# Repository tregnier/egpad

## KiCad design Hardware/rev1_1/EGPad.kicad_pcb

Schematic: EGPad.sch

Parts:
C1, C2, C3, C4, C5, C6: 10nF; C_0603
D1, D2, D3, D4, D5, D6, D7, D8, D9, D10, D11, D12, D13, D14, D15, D16, D17, D18, D19, D20: D_Small; MD_Diode
J1: OLED
JP1, JP2, JP3, JP4, JP5, JP6, JP7, JP8: Jmp; Jumper
MX1, MX2, MX3, MX4, MX6, MX7, MX8, MX9, MX10, MX11, MX12, MX13, MX14, MX15: MX-NoLED; MX_ALPS_PG1350_noLed
MX5: MX-NoLED; MX-2U-NoLED
MX16, MX17: MX-NoLED; Hybrid_PCB_200V
R1, R2, R3, R4, R5, R6, R7, R8, R9, R10, R11, R12: 10k; Resistor
R13, R14: R
RSW1: SW_Push; ResetSW
SW1, SW2, SW3: Rotary_Encoder_Switch; RotaryEncoder_EC11
U1: ProMicro; ProMicro_v2

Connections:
A1: C1.1, R1.1, U1.1
A2: C3.1, R3.1, U1.2
A3: C5.1, R5.1, U1.7
B1: C2.1, R2.1, U1.20
B2: C4.1, R4.1, U1.19
B3: C6.1, R6.1, U1.18
COL1: MX1.1 (COL), MX2.1 (COL), MX3.1 (COL), MX4.1 (COL), MX5.1 (COL), U1.8
COL2: MX6.1 (COL), MX7.1 (COL), MX8.1 (COL), MX9.1 (COL), MX10.1 (COL), U1.9
COL3: MX11.1 (COL), MX12.1 (COL), MX13.1 (COL), MX14.1 (COL), U1.10
COL4: MX15.1 (COL), MX16.1 (COL), MX17.1 (COL), U1.11
COL5: SW1.S1, SW2.S1, SW3.S1, U1.12
GND: C1.2, C2.2, C3.2, C4.2, C5.2, C6.2, JP1.2, JP8.2, RSW1.2, SW1.C, SW2.C, SW3.C, U1.3, U1.4, U1.23
unnamed: D1.2, MX1.2 (ROW)
unnamed: D2.2, MX2.2 (ROW)
unnamed: D3.2, MX3.2 (ROW)
unnamed: D4.2, MX4.2 (ROW)
unnamed: D5.2, MX5.2 (ROW)
unnamed: D6.2, MX6.2 (ROW)
unnamed: D7.2, MX7.2 (ROW)
unnamed: D8.2, MX8.2 (ROW)
unnamed: D9.2, MX9.2 (ROW)
unnamed: D10.2, MX10.2 (ROW)
unnamed: D11.2, MX11.2 (ROW)
unnamed: D12.2, MX12.2 (ROW)
unnamed: D13.2, MX13.2 (ROW)
unnamed: D14.2, MX14.2 (ROW)
unnamed: D15.2, MX15.2 (ROW)
unnamed: D16.2, MX16.2 (ROW)
unnamed: D17.2, MX17.2 (ROW)
unnamed: D18.2, SW1.S2
unnamed: D19.2, SW2.S2
unnamed: D20.2, SW3.S2
unnamed: J1.1, JP4.1, JP8.1
unnamed: J1.2, JP3.1, JP7.1
unnamed: J1.3, JP2.1, JP6.1
unnamed: J1.4, JP1.1, JP5.1
unnamed: R1.2, R7.2, SW1.A
unnamed: R2.2, R8.2, SW1.B
unnamed: R3.2, R9.2, SW2.A
unnamed: R4.2, R10.2, SW2.B
unnamed: R5.2, R11.2, SW3.A
unnamed: R6.2, R12.2, SW3.B
ROW1: D1.1, D6.1, D11.1, D15.1, D18.1, U1.13
ROW2: D2.1, D7.1, D12.1, D16.1, D19.1, U1.14
ROW3: D3.1, D8.1, D13.1, D17.1, D20.1, U1.15
ROW4: D4.1, D9.1, D14.1, U1.16
ROW5: D5.1, D10.1, U1.17
SCL: JP3.2, JP6.2, R14.1, U1.6
SDA: JP4.2, JP5.2, R13.1, U1.5
VCC: JP2.2, JP7.2, R7.1, R8.1, R9.1, R10.1, R11.1, R12.1, R13.2, R14.2, U1.21
reset: RSW1.1, U1.22

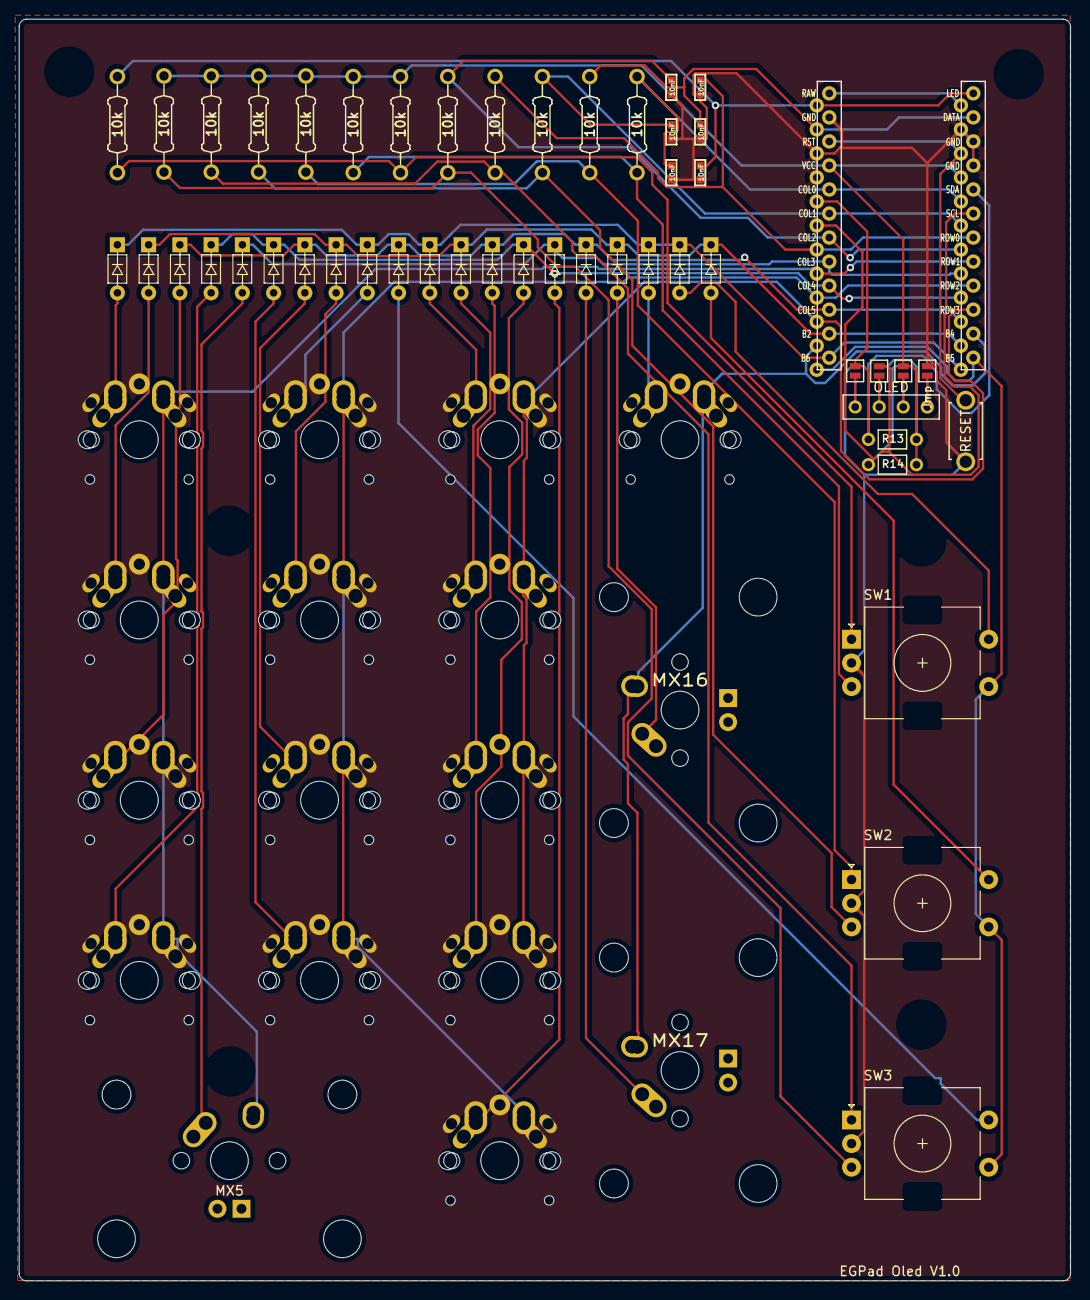
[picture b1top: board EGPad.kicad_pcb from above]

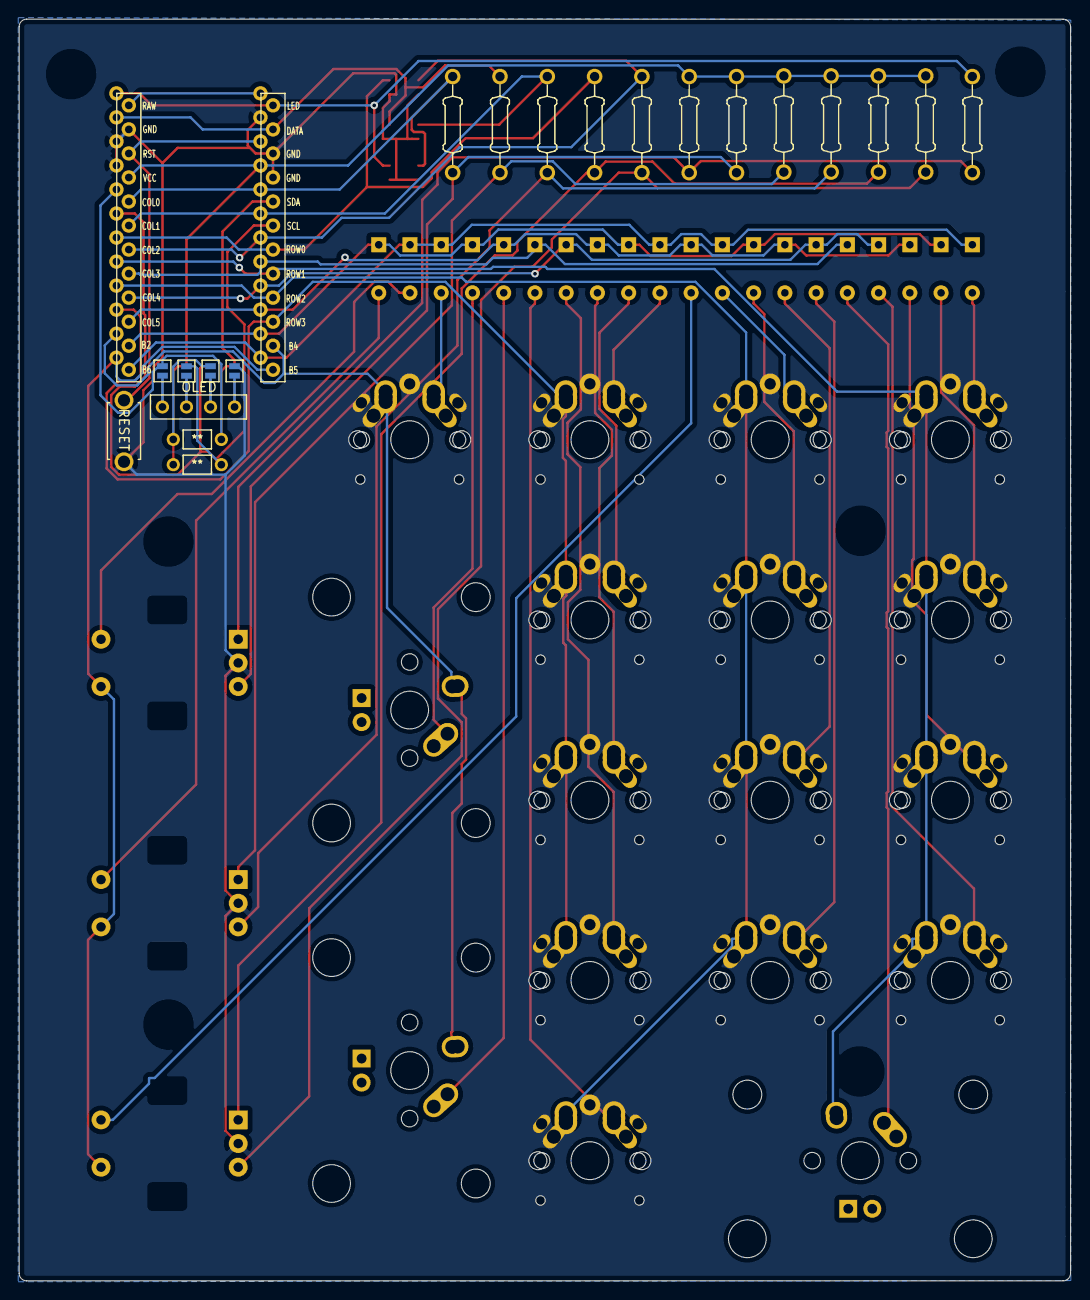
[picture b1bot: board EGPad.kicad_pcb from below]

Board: 2 copper layers, 111.1 x 133.3 mm, 71 parts (4 on the bottom side), 51 nets.

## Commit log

2021-10-29 adding oled from Corne style and reverse PCB
2021-10-30 optimization and gerber for production
2021-11-10 egpad oled gerber file v1.0
2021-11-10 clean up
2021-11-10 adding rev 1_1 for sapping face on switch too
2021-11-26 add acrylic cover
2022-01-27 adding spacer to hardware
